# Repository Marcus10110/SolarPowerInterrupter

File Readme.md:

# Solar Power Interrupter PCB

## Purpose

We will be charging the camp battery from both solar and generators. However, we do not want to attempt to charge the battery from two source at once, since they are unable to cooperate.
To avoid this situation, the solar charger should automatically be disengaged when the generator is turned on.
The solar charger connection instructions says to connect the battery before the solar panels. Therefore to turn off the solar charger, we should disconnect the panels from the solar charger.

This connection is approximately a maximum of 100V and 12A, DC.

The generator is detected by the presence of 5V from a USB charger connected to the generator.

When the 5V is not present, the relay should be conducting. The current required to turn on the relay will be provided by the battery.

The solar power interrupter will effectively logically invert the input from the USB charger, and switch on/off the relay using the battery voltage and a high side switch.

## Parts:

- P-channel MOSFET: BSS84
- N-channel MOSFET: BSS138

## Features:

- Input RC filter in case the USB-C input flickers on and off while the generator starts or stops.
- Polyfuse on USB input
- Polyfuse on battery input

## Review Points:

- Check Vgs and Vds absolute maximums, must survive max battery voltage (25V)
  - Vgs out of range on both!:
    - Fix: add voltage dividers. [Done]
- Check that the pin numbering in the schematic, PCB, and data sheet are consistent.
- Check relay behavior - do I need a current limiting resistor on the input? should one be added anyway for safety?
- Verify USB-C connector CC connections.
- Verify PCB silk screen matches connections.
- Is the battery safe from all failures?
- Is the 5V USB supply safe from all failures?
- All parts have part numbers!

# Images

Note, some small changes have been made since these images were captured.

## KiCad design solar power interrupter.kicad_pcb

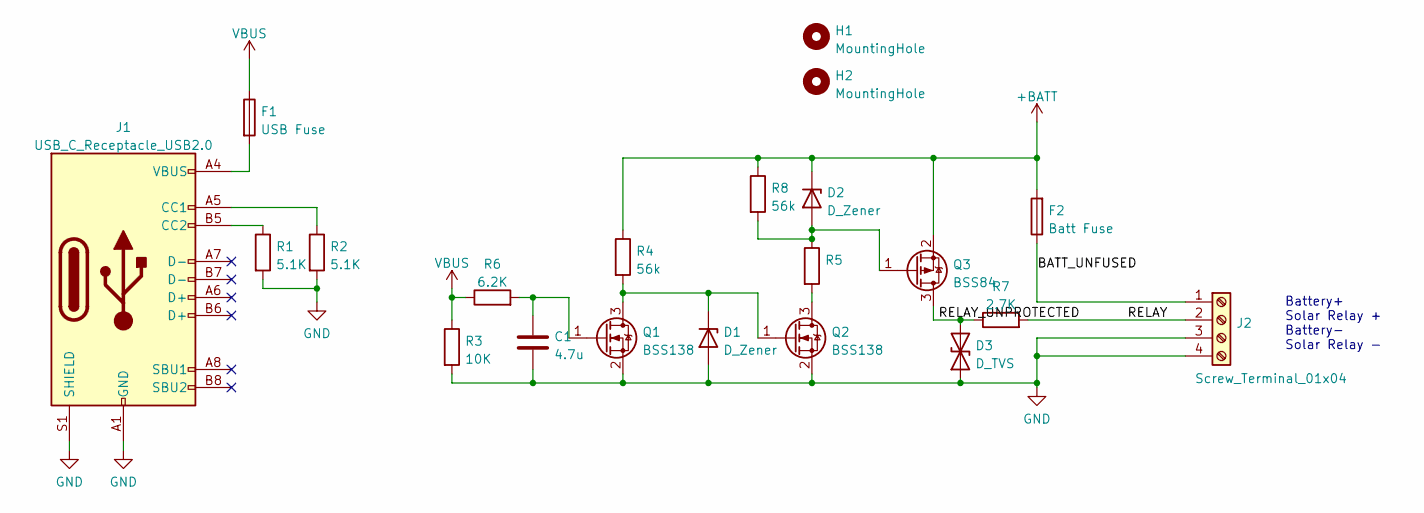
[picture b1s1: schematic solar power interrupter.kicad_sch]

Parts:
C1: 4.7u; C_0805_2012Metric
D1, D2: D_Zener; D_SOD-123
D3: D_TVS; D_SMB
F1: USB Fuse; Fuse_0805_2012Metric_Pad1.15x1.40mm_HandSolder
F2: Batt Fuse; Fuse_0805_2012Metric_Pad1.15x1.40mm_HandSolder
H1, H2: MountingHole; MountingHole_4.3mm_M4
J1: USB_C_Receptacle_USB2.0; USB_C_Receptacle_GCT_USB4085
J2: Screw_Terminal_01x04; TerminalBlock_Phoenix_MKDS-1,5-4_1x04_P5.00mm_Horizontal
Q1, Q2: BSS138; SOT-23
Q3: BSS84; SOT-23
R1, R2: 5.1K; R_0805_2012Metric
R3: 10K; R_0805_2012Metric
R4, R8: 56k; R_0805_2012Metric
R5: (no value)
R6: 6.2K; R_0805_2012Metric
R7: 2.7K; R_0805_2012Metric

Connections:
+BATT: D2.1 (K), F2.2, Q3.2 (S), R4.1, R8.1
/BATT_UNFUSED: F2.1, J2.1
/RELAY: J2.2, R7.2
/RELAY_UNPROTECTED: D3.2 (A2), Q3.3 (D), R7.1
GND: C1.2, D1.2 (A), D3.1 (A1), J1.A1 (GND), J1.A12 (GND), J1.B1 (GND), J1.B12 (GND), J1.S1 (SHIELD), J2.3, J2.4, Q1.2 (S), Q2.2 (S), R1.2, R2.2, R3.2
unnamed: C1.1, Q1.1 (G), R6.2
unnamed: D1.1 (K), Q1.3 (D), Q2.1 (G), R4.2
unnamed: D2.2 (A), Q3.1 (G), R5.1, R8.2
unnamed: F1.2, J1.A4 (VBUS), J1.A9 (VBUS), J1.B4 (VBUS), J1.B9 (VBUS)
unnamed: J1.A5 (CC1), R2.1
unnamed: J1.B5 (CC2), R1.1
unnamed: Q2.3 (D), R5.2
VBUS: F1.1, R3.1, R6.1

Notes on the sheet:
Battery+ Solar Relay + Battery- Solar Relay -

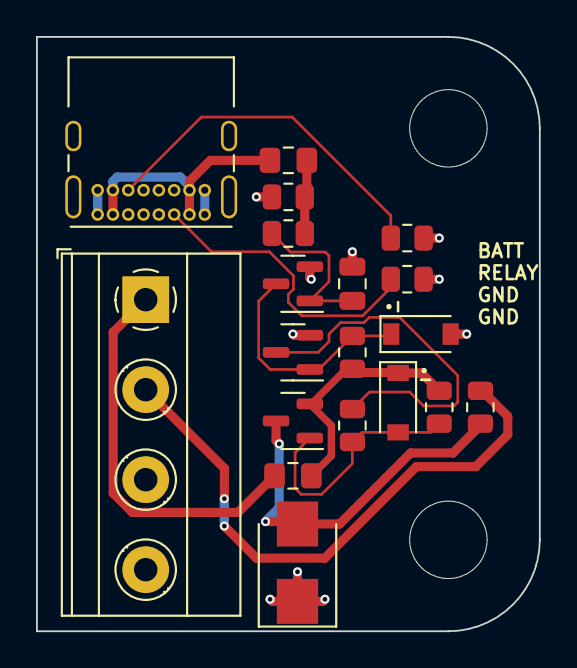
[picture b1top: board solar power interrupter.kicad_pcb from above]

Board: 2 copper layers, 27.9 x 33.0 mm, 21 parts (0 on the bottom side), 13 nets.

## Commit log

2022-08-09 added readme
2022-08-09 added KiCad project, LTSpice simulation, and git ignore.
2022-08-14 added protection to battery connection, changed pins on connector for safety, added zener diodes to limit Vgs, added protection for relay drive pin
2022-08-14 updated simulation added needed pullup resistor, note this wasn't included in the PCB that I ordered. added images to readme.
